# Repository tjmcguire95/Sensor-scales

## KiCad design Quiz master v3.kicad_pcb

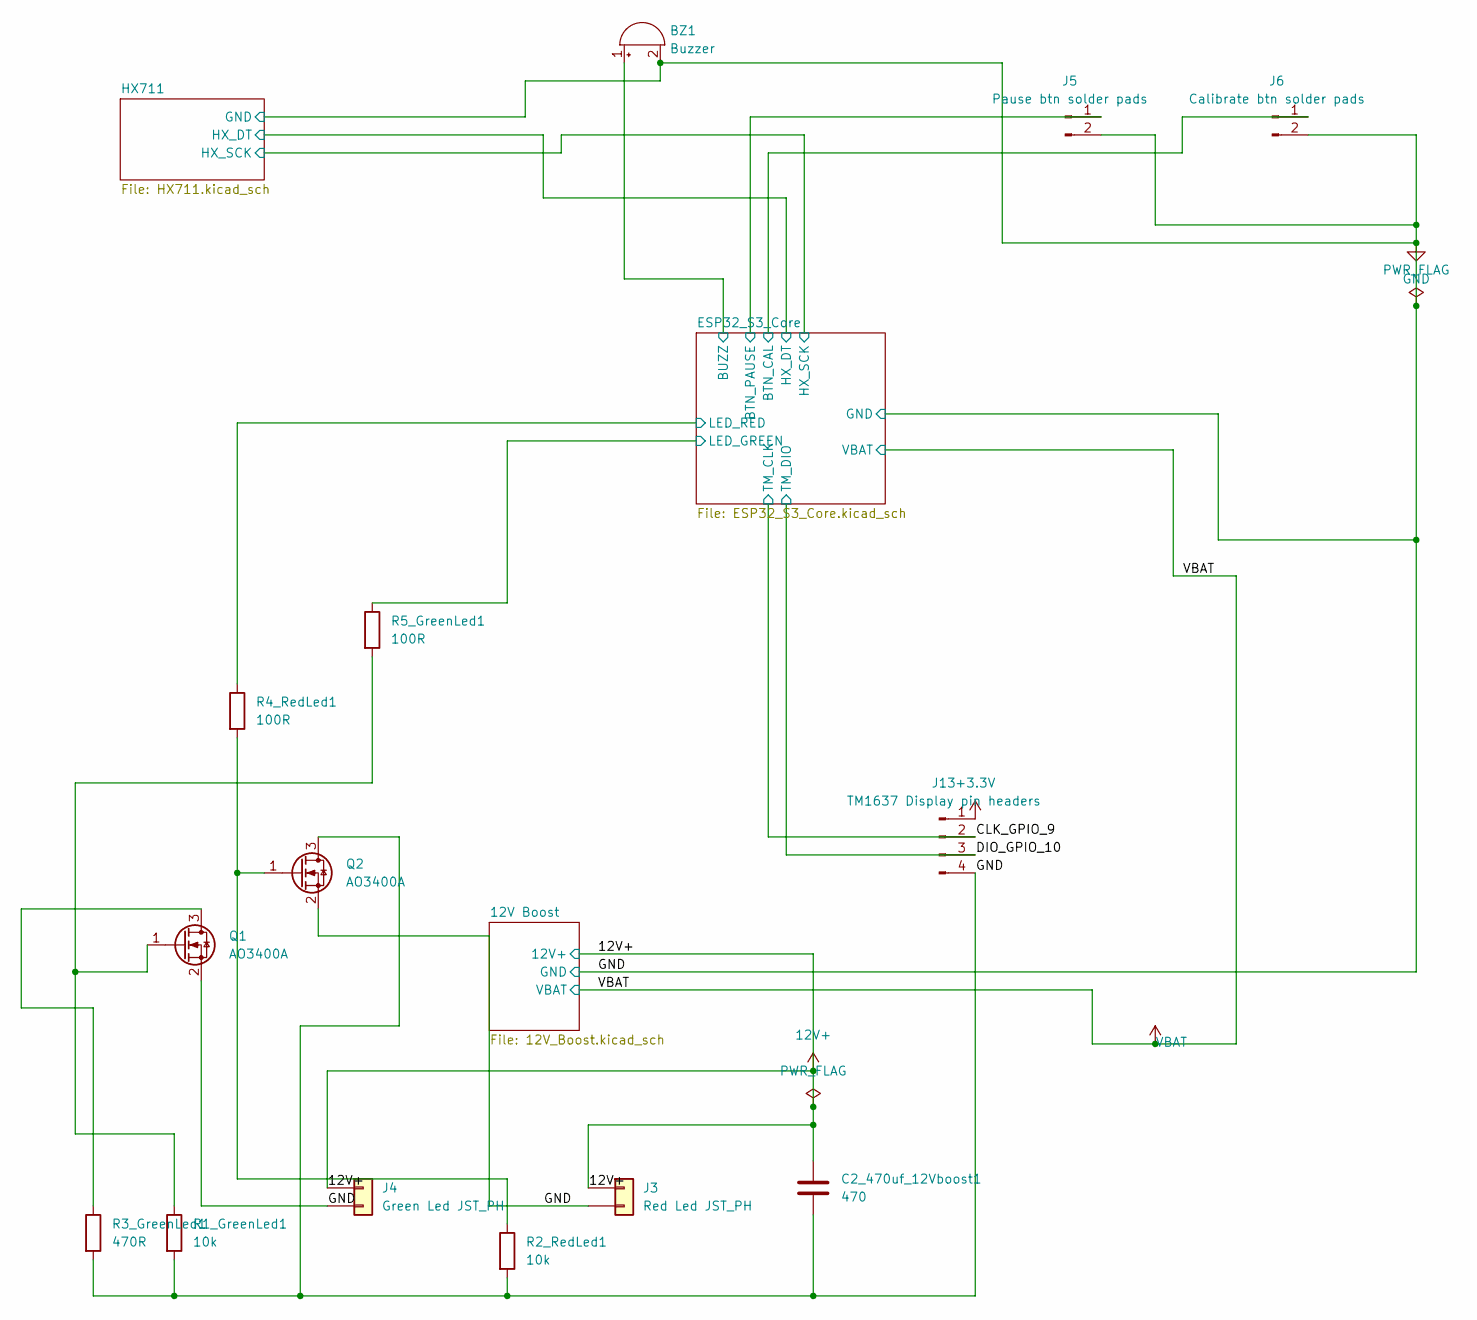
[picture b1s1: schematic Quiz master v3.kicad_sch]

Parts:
BZ1: Buzzer; Buzzer_12x9.5RM7.6
C2_470uf_12Vboost1: 470; CP_Radial_D8.0mm_P5.00mm
J3: Red Led JST_PH; JST_PH_B2B-PH-K_1x02_P2.00mm_Vertical
J4: Green Led JST_PH; JST_PH_B2B-PH-K_1x02_P2.00mm_Vertical
J5: Pause btn solder pads; SolderWire-0.5sqmm_1x02_P4.6mm_D0.9mm_OD2.1mm
J6: Calibrate btn solder pads; SolderWire-0.5sqmm_1x02_P4.6mm_D0.9mm_OD2.1mm
J13: TM1637 Display pin headers; JST_PH_B4B-PH-K_1x04_P2.00mm_Vertical
Q1, Q2: AO3400A; SOT-23
R1_GreenLed1, R2_RedLed1: 10k; R_0805_2012Metric; MPN RC0805FR-0710KL
R3_GreenLed1: 470R; R_0805_2012Metric; MPN RC0805FR-07470RL
R4_RedLed1, R5_GreenLed1: 100R; R_0805_2012Metric; MPN RC0805FR-07100RL

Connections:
12V+: C2_470uf_12Vboost1.1, J3.1, J4.1; also elsewhere on the board
+3.3V: J13.1; also elsewhere on the board
/CLK_GPIO_9: J13.2; also elsewhere on the board
/DIO_GPIO_10: J13.3; also elsewhere on the board
/ESP32_S3_Core/BTN_CAL: J6.1; also elsewhere on the board
/ESP32_S3_Core/BTN_PAUSE: J5.1; also elsewhere on the board
/ESP32_S3_Core/BUZZ: BZ1.1 (+); also elsewhere on the board
/ESP32_S3_Core/LED_GREEN: R5_GreenLed1.1; also elsewhere on the board
/ESP32_S3_Core/LED_RED: R4_RedLed1.1; also elsewhere on the board
GND: BZ1.2 (-), C2_470uf_12Vboost1.2, J3.2, J4.2, J5.2, J6.2, J13.4, Q1.2 (S), Q2.2 (S), Q2.3 (D), R1_GreenLed1.2, R2_RedLed1.2, R3_GreenLed1.2; also elsewhere on the board
unnamed: Q1.3 (D), R3_GreenLed1.1
unnamed: Q1.1 (G), R1_GreenLed1.1, R5_GreenLed1.2
unnamed: Q2.1 (G), R2_RedLed1.1, R4_RedLed1.2

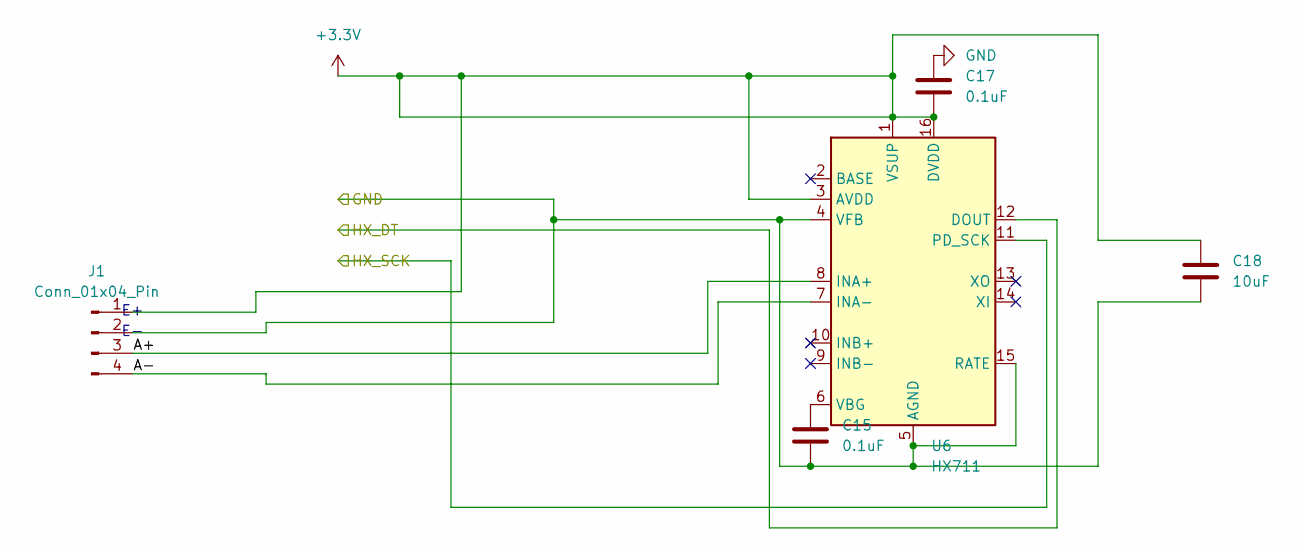
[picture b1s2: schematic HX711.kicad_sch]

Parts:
C15, C17: 0.1uF; C_0603_1608Metric
C18: 10uF; C_0805_2012Metric
J1: Conn_01x04_Pin; JST_PH_B4B-PH-K_1x04_P2.00mm_Vertical
U6: HX711; SOIC-16_3.9x9.9mm_P1.27mm

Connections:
+3.3V: C17.2, C18.1, J1.1, U6.1 (VSUP), U6.3 (AVDD), U6.16 (DVDD); also elsewhere on the board
/ESP32_S3_Core/HX_DT: U6.12 (DOUT); also elsewhere on the board
/ESP32_S3_Core/HX_SCK: U6.11 (PD_SCK); also elsewhere on the board
/HX711/A+: J1.3, U6.8 (INA+)
/HX711/A-: J1.4, U6.7 (INA-)
GND: C15.2, C17.1, C18.2, J1.2, U6.4 (VFB), U6.5 (AGND), U6.15 (RATE); also elsewhere on the board
unnamed: C15.1, U6.6 (VBG)

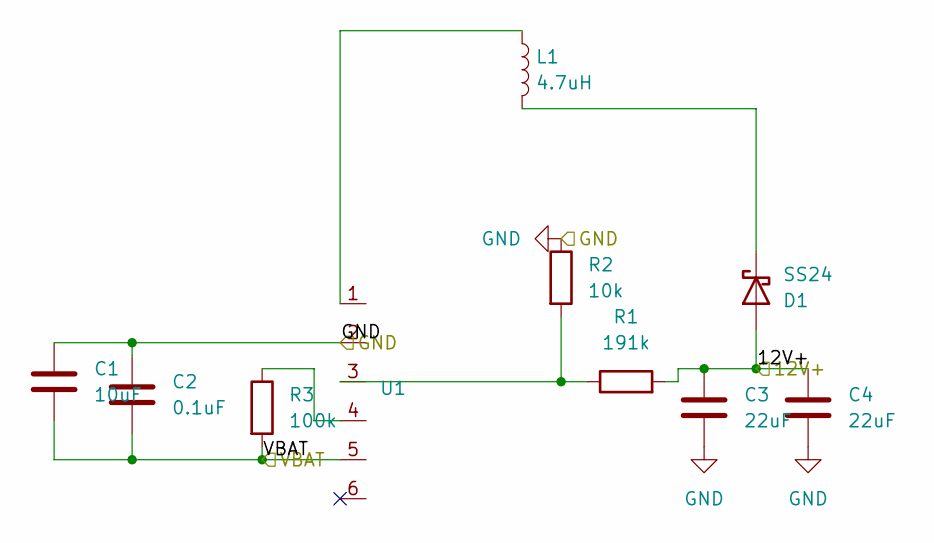
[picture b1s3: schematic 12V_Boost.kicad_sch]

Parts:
C1: 10uF; C_0805_2012Metric
C2: 0.1uF; C_0603_1608Metric
C3, C4: 22uF; C_1210_3225Metric
D1: SS24; D_SMA
L1: 4.7uH; L_6.3x6.3_H3
R1: 191k; R_0603_1608Metric
R2: 10k; R_0603_1608Metric
R3: 100k; R_0603_1608Metric
U1: SOT-23-6

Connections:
12V+: C3.1, C4.1, D1.2 (A), R1.2; also elsewhere on the board
GND: C1.1, C2.1, C3.2, C4.2, R2.1, U1.2 (GND); also elsewhere on the board
unnamed: D1.1 (K), L1.2
unnamed: R3.1, U1.4 (EN)
unnamed: R1.1, R2.2, U1.3 (FB)
unnamed: L1.1, U1.1 (SW)
VBAT: C1.2, C2.2, R3.2, U1.5 (IN); also elsewhere on the board

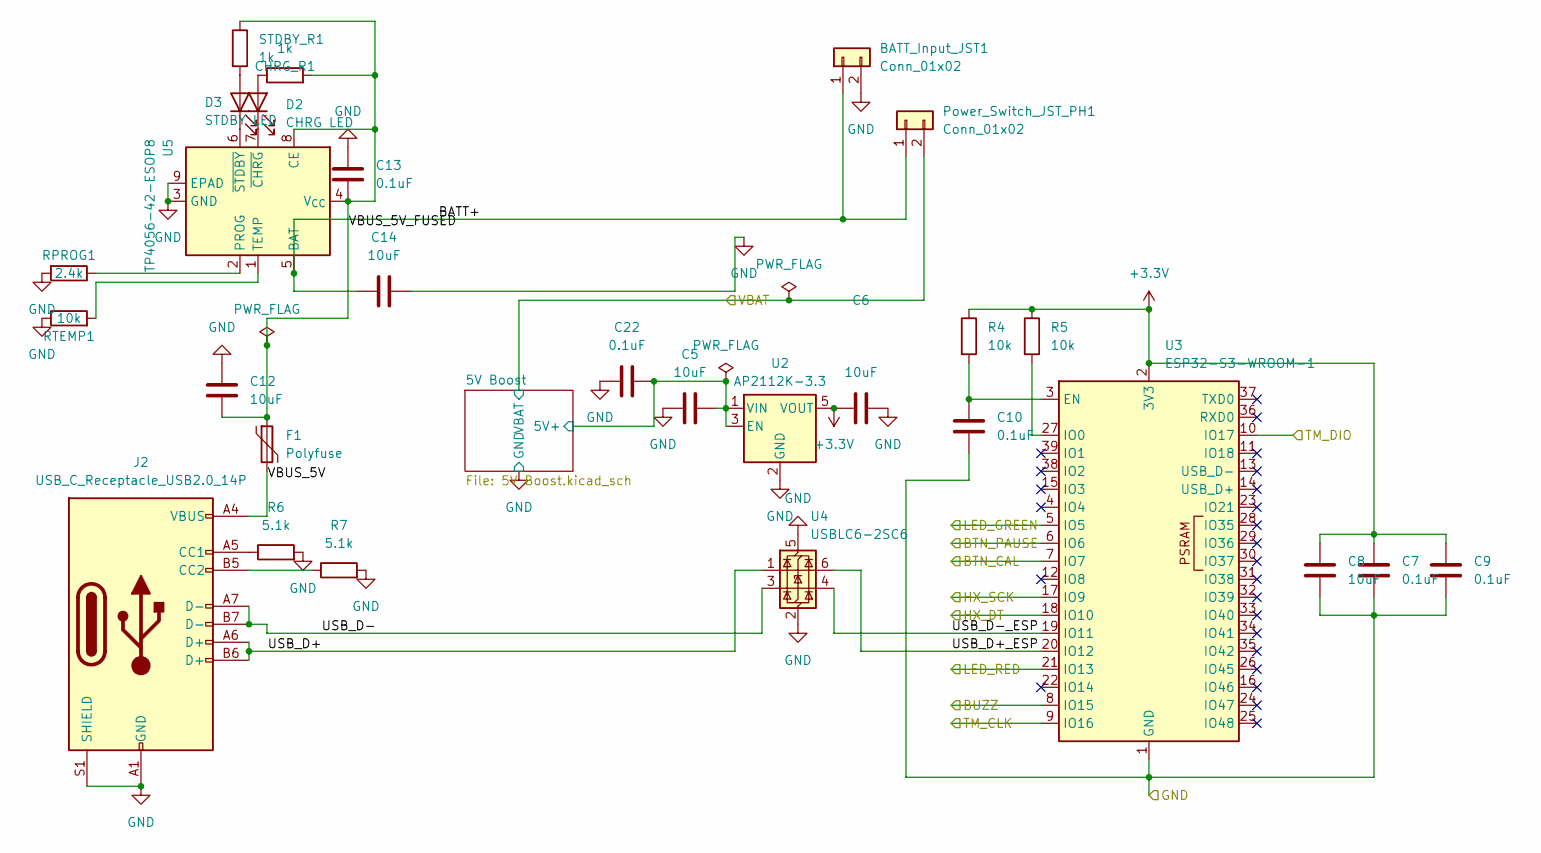
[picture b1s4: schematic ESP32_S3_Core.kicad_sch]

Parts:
BATT_Input_JST1: Conn_01x02; JST_PH_B2B-PH-K_1x02_P2.00mm_Vertical
C5, C6, C8, C12, C14: 10uF; C_0805_2012Metric
C7, C9, C10, C13, C22: 0.1uF; C_0603_1608Metric
CHRG_R1: 1k; R_0603_1608Metric
D2: CHRG LED; SolderWire-0.5sqmm_1x02_P4.8mm_D0.9mm_OD2.3mm
D3: STDBY LED; SolderWire-0.5sqmm_1x02_P4.8mm_D0.9mm_OD2.3mm
F1: Polyfuse; Fuse_1206_3216Metric
J2: USB_C_Receptacle_USB2.0_14P; USB_C_Receptacle_HRO_TYPE-C-31-M-12
Power_Switch_JST_PH1: Conn_01x02; JST_PH_B2B-PH-K_1x02_P2.00mm_Vertical
R4, R5: 10k; R_0603_1608Metric
R6, R7: 5.1k; R_0603_1608Metric
RPROG1: 2.4k; R_0603_1608Metric
RTEMP1: 10k; R_0603_1608Metric
STDBY_R1: 1k; R_0603_1608Metric
U2: AP2112K-3.3; SOT-23-5
U3: ESP32-S3-WROOM-1
U4: USBLC6-2SC6; SOT-23-6
U5: TP4056-42-ESOP8; SOIC-8-1EP_3.9x4.9mm_P1.27mm_EP2.41x3.3mm_ThermalVias

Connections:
+3.3V: C6.2, C7.1, C8.1, C9.1, R4.1, R5.1, U2.5 (VOUT), U3.2 (3V3); also elsewhere on the board
/CLK_GPIO_9: U3.9 (IO16); also elsewhere on the board
/DIO_GPIO_10: U3.10 (IO17); also elsewhere on the board
/ESP32_S3_Core/5V Boost/5V+: C5.2, C22.2, U2.1 (VIN), U2.3 (EN); also elsewhere on the board
/ESP32_S3_Core/BATT+: BATT_Input_JST1.1, C14.2, Power_Switch_JST_PH1.1, U5.5 (BAT); also elsewhere on the board
/ESP32_S3_Core/BTN_CAL: U3.7 (IO7); also elsewhere on the board
/ESP32_S3_Core/BTN_PAUSE: U3.6 (IO6); also elsewhere on the board
/ESP32_S3_Core/BUZZ: U3.8 (IO15); also elsewhere on the board
/ESP32_S3_Core/HX_DT: U3.18 (IO10); also elsewhere on the board
/ESP32_S3_Core/HX_SCK: U3.17 (IO9); also elsewhere on the board
/ESP32_S3_Core/LED_GREEN: U3.5 (IO5); also elsewhere on the board
/ESP32_S3_Core/LED_RED: U3.21 (IO13); also elsewhere on the board
/ESP32_S3_Core/USB_D+: J2.A6 (D+), J2.B6 (D+), U4.1 (I/O1)
/ESP32_S3_Core/USB_D+_ESP: U3.20 (IO12), U4.6 (I/O1)
/ESP32_S3_Core/USB_D-: J2.A7 (D-), J2.B7 (D-), U4.3 (I/O2)
/ESP32_S3_Core/USB_D-_ESP: U3.19 (IO11), U4.4 (I/O2)
/ESP32_S3_Core/VBUS_5V: F1.2, J2.A4 (VBUS), J2.A9 (VBUS), J2.B4 (VBUS), J2.B9 (VBUS)
/ESP32_S3_Core/VBUS_5V_FUSED: C12.2, C13.2, CHRG_R1.2, F1.1, STDBY_R1.1, U5.4 (V_{CC}), U5.8 (CE)
GND: BATT_Input_JST1.2, C5.1, C6.1, C7.2, C8.2, C9.2, C10.2, C12.1, C13.1, C14.1, C22.1, J2.A1 (GND), J2.A12 (GND), J2.B1 (GND), J2.B12 (GND), J2.S1 (SHIELD), R6.2, R7.2, RPROG1.2, RTEMP1.1, U2.2 (GND), U3.1 (GND), U3.40 (GND), U3.41 (GND), U4.2 (GND), U4.5 (VBUS), U5.3 (GND), U5.9 (EPAD); also elsewhere on the board
unnamed: CHRG_R1.1, D2.2 (A)
unnamed: D2.1 (K), U5.7 (~CHRG)
unnamed: D3.2 (A), STDBY_R1.2
unnamed: D3.1 (K), U5.6 (~STDBY)
unnamed: J2.A5 (CC1), R6.1
unnamed: J2.B5 (CC2), R7.1
unnamed: C10.1, R4.2, U3.3 (EN)
unnamed: R5.2, U3.27 (IO0)
unnamed: RPROG1.1, U5.2 (PROG)
unnamed: RTEMP1.2, U5.1 (TEMP)

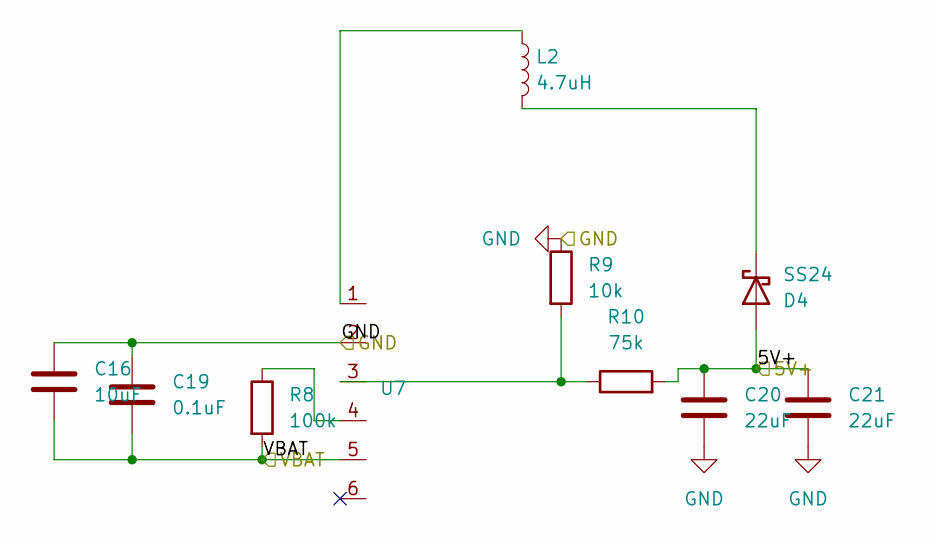
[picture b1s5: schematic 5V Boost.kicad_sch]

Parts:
C16: 10uF; C_0805_2012Metric
C19: 0.1uF; C_0603_1608Metric
C20, C21: 22uF; C_1210_3225Metric
D4: SS24; D_SMA
L2: 4.7uH; L_6.3x6.3_H3
R8: 100k; R_0603_1608Metric
R9: 10k; R_0603_1608Metric
R10: 75k; R_0603_1608Metric
U7: SOT-23-6

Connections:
/ESP32_S3_Core/5V Boost/5V+: C20.1, C21.1, D4.2 (A), R10.2; also elsewhere on the board
GND: C16.1, C19.1, C20.2, C21.2, R9.1, U7.2 (GND); also elsewhere on the board
unnamed: D4.1 (K), L2.2
unnamed: R8.1, U7.4 (EN)
unnamed: R9.2, R10.1, U7.3 (FB)
unnamed: L2.1, U7.1 (SW)
VBAT: C16.2, C19.2, R8.2, U7.5 (IN); also elsewhere on the board

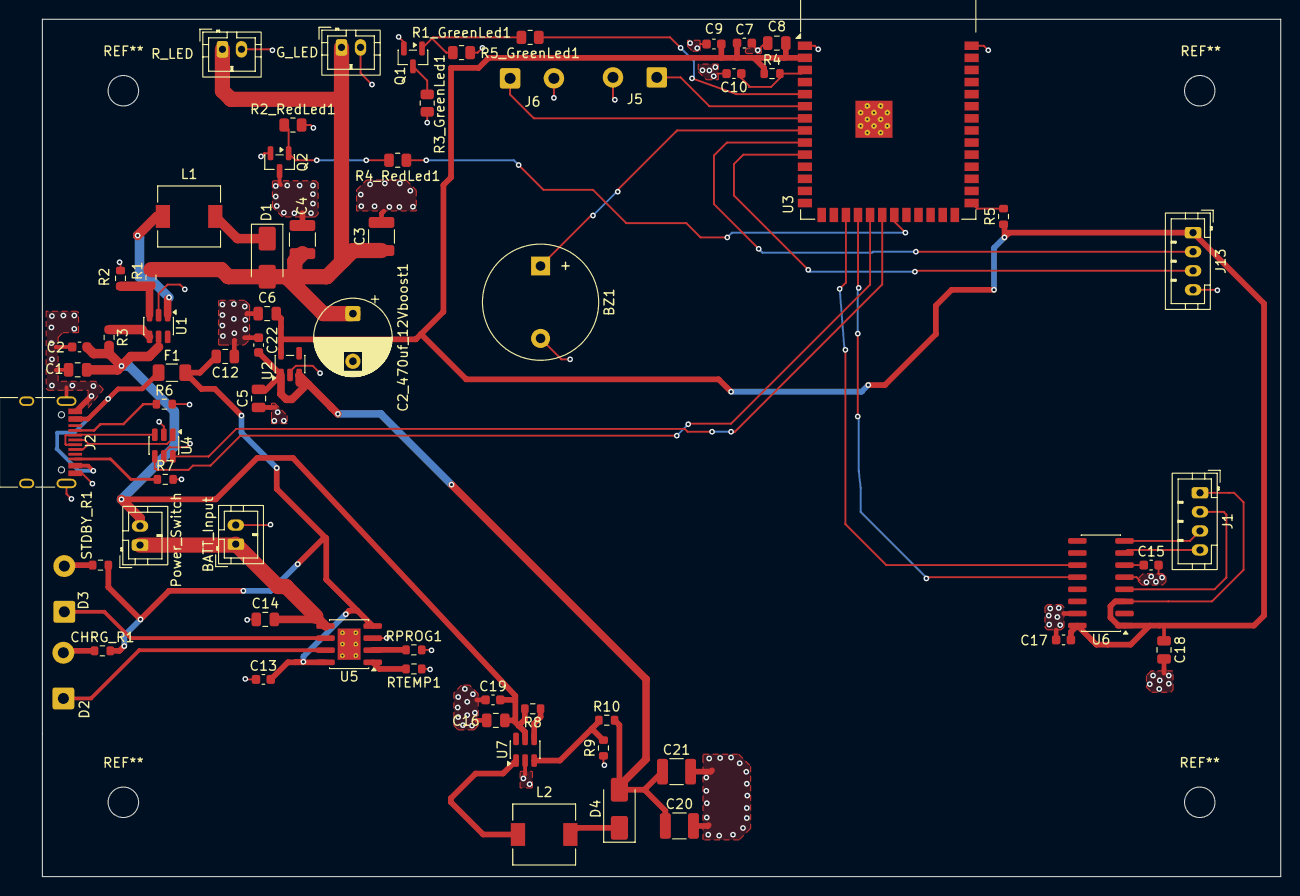
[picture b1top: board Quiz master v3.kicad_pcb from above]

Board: 2 copper layers, 130.0 x 90.0 mm, 67 parts (0 on the bottom side), 45 nets.

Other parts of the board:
BATT_Input: Conn_01x02; JST_PH_B2B-PH-K_1x02_P2.00mm_Vertical
G_LED: Green Led JST_PH; JST_PH_B2B-PH-K_1x02_P2.00mm_Vertical
Power_Switch: Conn_01x02; JST_PH_B2B-PH-K_1x02_P2.00mm_Vertical
R_LED: Red Led JST_PH; JST_PH_B2B-PH-K_1x02_P2.00mm_Vertical

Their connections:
12V+: G_LED.1, R_LED.1; also elsewhere on the board
/ESP32_S3_Core/BATT+: BATT_Input.1, Power_Switch.1; also elsewhere on the board
GND: BATT_Input.2, G_LED.2, R_LED.2; also elsewhere on the board
VBAT: Power_Switch.2; also elsewhere on the board

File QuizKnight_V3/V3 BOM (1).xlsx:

Reference | Qty | Value | DNP | Exclude from BOM | Exclude from Board | Footprint | Datasheet | Description | Supplier | Supplier Part Number | MPN | Manufacturer
BATT_Input_JST1,Power_Switch_JST_PH1 | 2.0 | Conn_01x02 |  |  |  | Connector_JST:JST_PH_B2B-PH-K_1x02_P2.00mm_Vertical | ~ | Generic connector, single row, 01x02, script generated (kicad-library-utils/sch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
BOOT1,RESET1 | 2.0 | SW_Push |  |  |  | Button_Switch_SMD:SW_SPST_TL3342 | ~ | Push button switch, generic, two pins
BZ1 | 1.0 | Buzzer |  |  |  | Buzzer_Beeper:Buzzer_12x9.5RM7.6 | ~ | Buzzer, polarized
C1,C5,C6,C8,C12,C14,C16,C18 | 8.0 | 10uF |  |  |  | Capacitor_SMD:C_0805_2012Metric | ~ | Unpolarized capacitor
C2,C7,C9,C10,C13,C15,C17,C19,C22 | 9.0 | 0.1uF |  |  |  | Capacitor_SMD:C_0603_1608Metric | ~ | Unpolarized capacitor
C2_470uf_12Vboost1 | 1.0 | 470.0 |  |  |  | Capacitor_THT:CP_Radial_D8.0mm_P5.00mm | ~ | Unpolarized capacitor_12V rail-GND
C3,C4,C20,C21 | 4.0 | 22uF |  |  |  | Capacitor_SMD:C_1210_3225Metric | ~ | Unpolarized capacitor
CHRG_R1,STDBY_R1 | 2.0 | 1k |  |  |  | Resistor_SMD:R_0603_1608Metric | ~ | Resistor
D1,D4 | 2.0 | SS24 |  |  |  | Diode_SMD:D_SMA | https://www.vishay.com/docs/88748/ss22.pdf | 40V 2A Schottky Diode, SMA
D2 | 1.0 | CHRG LED |  |  |  | Connector_Wire:SolderWire-0.5sqmm_1x02_P4.8mm_D0.9mm_OD2.3mm | ~ | Light emitting diode
D3 | 1.0 | STDBY LED |  |  |  | Connector_Wire:SolderWire-0.5sqmm_1x02_P4.8mm_D0.9mm_OD2.3mm | ~ | Light emitting diode
F1 | 1.0 | Polyfuse |  |  |  | Fuse:Fuse_1206_3216Metric | ~ | Resettable fuse, polymeric positive temperature coefficient
J1 | 1.0 | Conn_01x04_Pin |  |  |  | Connector_JST:JST_PH_B4B-PH-K_1x04_P2.00mm_Vertical | ~ | Generic connector, single row, 01x04, script generated
J2 | 1.0 | USB_C_Receptacle_USB2.0_14P |  |  |  | Connector_USB:USB_C_Receptacle_HRO_TYPE-C-31-M-12 | https://www.usb.org/sites/default/files/documents/usb_type-c.zip | USB 2.0-only 14P Type-C Receptacle connector
J3 | 1.0 | Red Led JST_PH |  |  |  | Connector_JST:JST_PH_B2B-PH-K_1x02_P2.00mm_Vertical | ~ | Generic connector, single row, 01x02, script generated (kicad-library-utils/sch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
J4 | 1.0 | Green Led JST_PH |  |  |  | Connector_JST:JST_PH_B2B-PH-K_1x02_P2.00mm_Vertical | ~ | Generic connector, single row, 01x02, script generated (kicad-library-utils/sch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
J5 | 1.0 | Pause btn solder pads |  |  |  | Connector_Wire:SolderWire-0.5sqmm_1x02_P4.6mm_D0.9mm_OD2.1mm | ~ | Generic connector, single row, 01x02, script generated
J6 | 1.0 | Calibrate btn solder pads |  |  |  | Connector_Wire:SolderWire-0.5sqmm_1x02_P4.6mm_D0.9mm_OD2.1mm | ~ | Generic connector, single row, 01x02, script generated
J13 | 1.0 | TM1637 Display pin headers |  |  |  | Connector_JST:JST_PH_B4B-PH-K_1x04_P2.00mm_Vertical | ~ | Generic connector, single row, 01x04, script generated
L1,L2 | 2.0 | 4.7uH |  |  |  | Inductor_SMD:L_6.3x6.3_H3 | ~ | Inductor
Q1,Q2 | 2.0 | AO3400A |  |  |  | Package_TO_SOT_SMD:SOT-23 | http://www.aosmd.com/pdfs/datasheet/AO3400A.pdf | 30V Vds, 5.7A Id, N-Channel MOSFET, SOT-23
R1 | 1.0 | 191k |  |  |  | Resistor_SMD:R_0603_1608Metric | ~ | Resistor
R1_GreenLed1,R2_RedLed1 | 2.0 | 10k |  |  |  | Resistor_SMD:R_0805_2012Metric | ~ | Resistor | Mouser | 603-RC0805FR-0710KL | RC0805FR-0710KL | Yageo
R2,R4,R5,R9,RTEMP1 | 5.0 | 10k |  |  |  | Resistor_SMD:R_0603_1608Metric | ~ | Resistor
R3,R8 | 2.0 | 100k |  |  |  | Resistor_SMD:R_0603_1608Metric | ~ | Resistor
R3_GreenLed1 | 1.0 | 470R |  |  |  | Resistor_SMD:R_0805_2012Metric | ~ | Resistor | Mouser | 603-RC0805FR-07470RL | RC0805FR-07470RL | Yageo
R4_RedLed1,R5_GreenLed1 | 2.0 | 100R |  |  |  | Resistor_SMD:R_0805_2012Metric | ~ | Resistor | Mouser | 603-RC0805FR-07100RL | RC0805FR-07100RL | Yageo
R6,R7 | 2.0 | 5.1k |  |  |  | Resistor_SMD:R_0603_1608Metric | ~ | Resistor
R10 | 1.0 | 75k |  |  |  | Resistor_SMD:R_0603_1608Metric | ~ | Resistor
RPROG1 | 1.0 | 2.4k |  |  |  | Resistor_SMD:R_0603_1608Metric | ~ | Resistor
U1,U7 | 2.0 | ~ |  |  |  | Package_TO_SOT_SMD:SOT-23-6
U2 | 1.0 | AP2112K-3.3 |  |  |  | Package_TO_SOT_SMD:SOT-23-5 | https://www.diodes.com/assets/Datasheets/AP2112.pdf | 600mA low dropout linear regulator, with enable pin, 3.8V-6V input voltage rang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
U3 | 1.0 | ESP32-S3-WROOM-1 |  |  |  | RF_Module:ESP32-S3-WROOM-1 | https://www.espressif.com/sites/default/files/documentation/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 | RF Module, ESP32-S3 SoC, Wi-Fi 802.11b/g/n, Bluetooth, BLE, 32-bit, 3.3V, onboa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
U4 | 1.0 | USBLC6-2SC6 |  |  |  | Package_TO_SOT_SMD:SOT-23-6 | https://www.st.com/resource/en/datasheet/usblc6-2.pdf | Very low capacitance ESD protection diode, 2 data-line, SOT-23-6
U5 | 1.0 | TP4056-42-ESOP8 |  |  |  | Package_SO:SOIC-8-1EP_3.9x4.9mm_P1.27mm_EP2.41x3.3mm_ThermalVias | https://www.lcsc.com/datasheet/lcsc_datasheet_2410121619_TOP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 | 1A Standalone Linear Li-ion/LiPo single-cell battery charger, 4.2V ±1% charge v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
U6 | 1.0 | HX711 |  |  |  | Package_SO:SOIC-16_3.9x9.9mm_P1.27mm | https://web.archive.org/web/20220615044707/https://akizukide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 | 24-bit Analog-to-Digital Converter (ADC) for Weight Scales, SOIC-16 (SOP-16)
